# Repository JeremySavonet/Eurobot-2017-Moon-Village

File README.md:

# WestBot - MainBoard Github page

## Description
TODO

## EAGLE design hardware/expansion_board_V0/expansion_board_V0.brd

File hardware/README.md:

Hardware section:
====

TODO: XXX

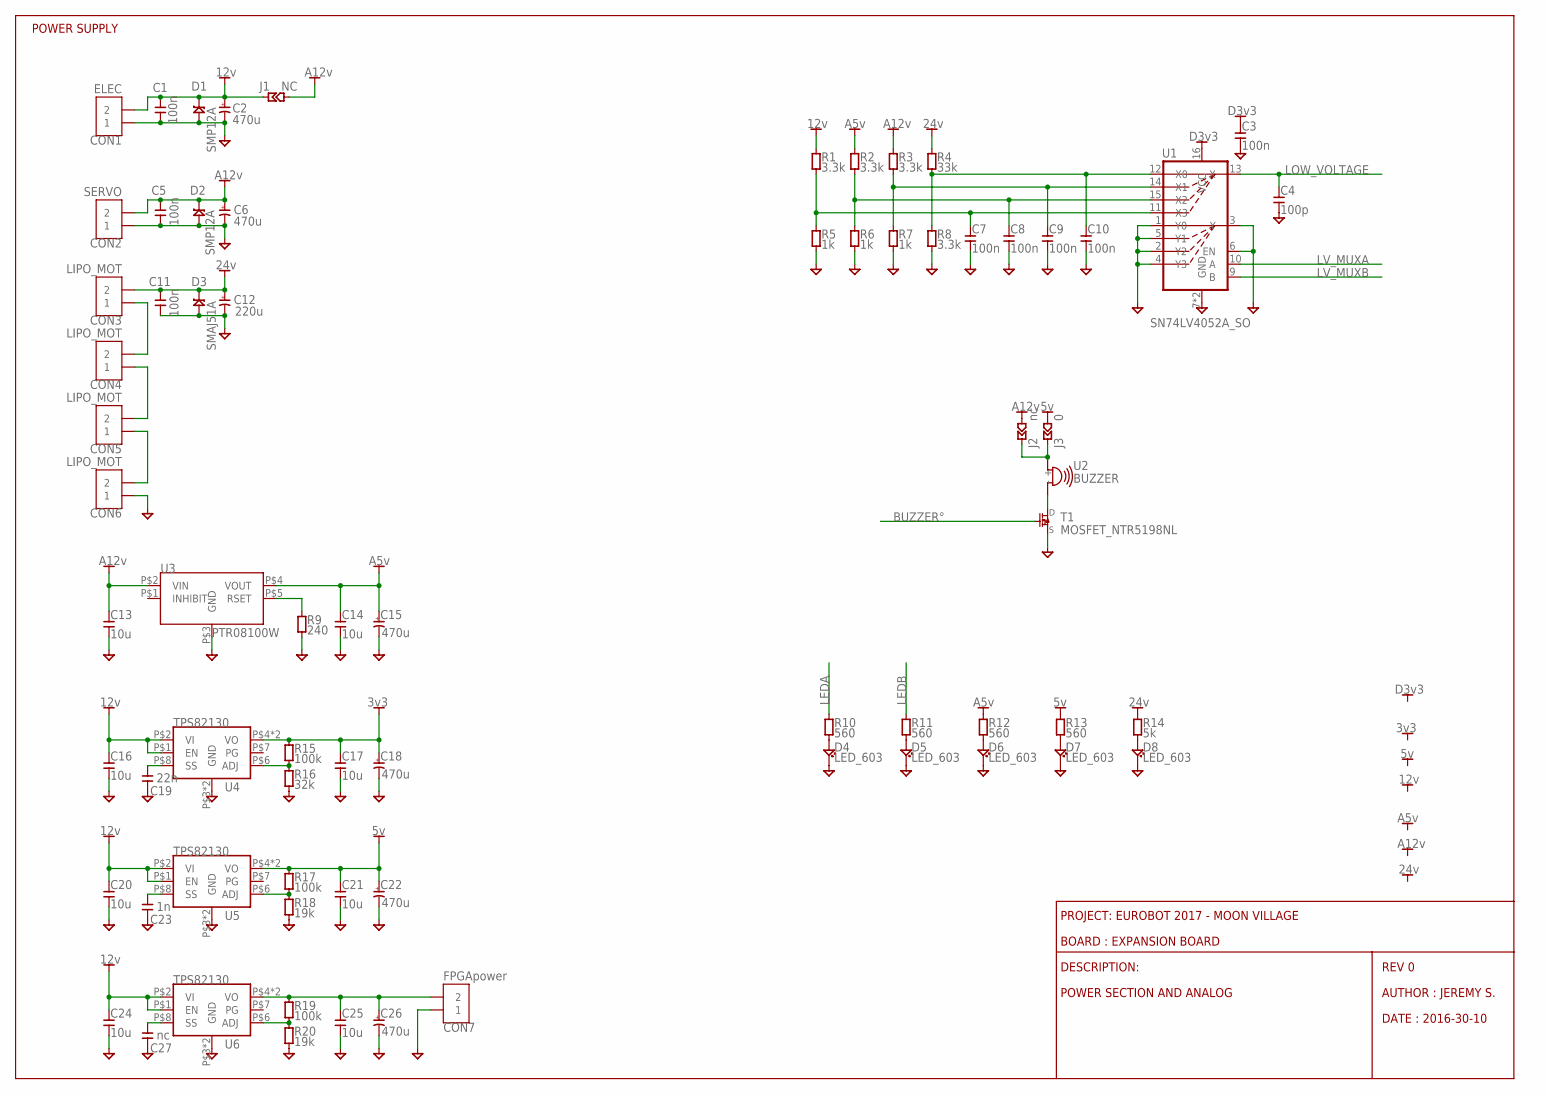
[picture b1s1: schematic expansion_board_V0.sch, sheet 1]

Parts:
C1, C3, C5, C7, C8, C9, C10: 100n; CAPC1005X55N
C2, C6, C15, C18, C22, C26: 470u; CAPAE835X1020N
C4: 100p; CAPC1005X55N
C11: 100n; CAPC2013X100N
C12: 220u; CAPAE835X1020N
C13, C14, C16, C17, C20, C21, C24, C25: 10u; CAPC2013X100N
C19: 22n; CAPC1005X55N
C23: 1n; CAPC1005X55N
C27: nc; CAPC1005X55N
CON1: ELEC; PHOENIX381P900X920-2N
CON2: SERVO; PHOENIX381P900X920-2N
CON3, CON4, CON5, CON6: LIPO_MOT; PHOENIX381P900X920-2N
CON7: FPGApower; PHOENIX381P900X920-2N
D1, D2: SMP12A; DO220AA
D3: SMAJ51A; D0214AC
D4, D5, D6, D7, D8: LED_603; LEDC1608X60N
J1: NC; JUMC1608X50AN
J2: nc; JUMC1005X50N
J3: 0; JUMC1005X50N
R1, R2, R3, R8: 3.3k; RESC1005X40N
R4: 33k; RESC1005X40N
R5, R6, R7: 1k; RESC1005X40N
R9: 240; RESC1005X40N
R10, R11, R12, R13: 560; RESC1005X40N
R14: 5k; RESC1005X40N
R15, R17, R19: 100k; RESC1005X40N
R16: 32k; RESC1005X40N
R18, R20: 19k; RESC1005X40N
T1: MOSFET_NTR5198NL; SOT95P290X130-3N
U1: SN74LV4052A_SO; SOIC127P780X200-16N
U2: BUZZER; BUZZER_CIRCLE
U3: PTR08100W
U4, U5, U6: TPS82130; SON65P310X290X153-9N

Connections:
3V3: C17.P$1, C18.+, R15.1, U4.P$4 (VO), U4.P$5 (VO); also elsewhere on the board
5V: C21.P$1, C22.+, J3.P$1 (1), R13.1, R17.1, U5.P$4 (VO), U5.P$5 (VO); also elsewhere on the board
12V: C1.1, C2.+, C16.P$1, C20.P$1, C24.P$1, CON1.P$2 (2), D1.C, J1.P$2 (2), R1.1, U4.P$1 (EN), U4.P$2 (VI), U5.P$1 (EN), U5.P$2 (VI), U6.P$1 (EN), U6.P$2 (VI); also elsewhere on the board
24V: C11.P$1, C12.+, CON3.P$2 (2), D3.C, R4.1, R14.1; also elsewhere on the board
A5V: C14.P$1, C15.+, R2.1, R12.1, U3.P$4 (VOUT); also elsewhere on the board
A12V: C5.1, C6.+, C13.P$1, CON2.P$2 (2), D2.C, J1.P$1 (1), J2.P$1 (1), R3.1, U3.P$2 (VIN); also elsewhere on the board
BUZZER°: T1.P$1 (G); also elsewhere on the board
D3V3: C3.1, U1.16 (VCC); also elsewhere on the board
GND: C1.2, C2.-, C3.2, C4.2, C5.2, C6.-, C7.2, C8.2, C9.2, C10.2, C11.P$2, C12.-, C13.P$2, C14.P$2, C15.-, C16.P$2, C17.P$2, C18.-, C19.2, C20.P$2, C21.P$2, C22.-, C23.2, C24.P$2, C25.P$2, C26.-, C27.2, CON1.P$1 (1), CON2.P$1 (1), CON6.P$1 (1), CON7.P$1 (1), D1.A, D2.A, D3.A, D4.C, D5.C, D6.C, D7.C, D8.C, R5.2, R6.2, R7.2, R8.2, R9.2, R16.2, R18.2, R20.2, T1.P$2 (S), U1.1 (Y0), U1.2 (Y2), U1.3 (Y), U1.4 (Y3), U1.5 (Y1), U1.6 (EN), U1.7 (GND), U1.8 (GND), U3.P$3 (GND), U4.P$3 (GND), U4.P$9 (GND), U5.P$3 (GND), U5.P$9 (GND), U6.P$3 (GND), U6.P$9 (GND); also elsewhere on the board
LEDA: R10.1; also elsewhere on the board
LEDB: R11.1; also elsewhere on the board
LOW_VOLTAGE: C4.1, U1.13 (X); also elsewhere on the board
LV_MUXA: U1.10 (A); also elsewhere on the board
LV_MUXB: U1.9 (B); also elsewhere on the board
unnamed: CON3.P$1 (1), CON4.P$2 (2)
unnamed: CON4.P$1 (1), CON5.P$2 (2)
unnamed: CON5.P$1 (1), CON6.P$2 (2)
unnamed: D6.A, R12.2
unnamed: R15.2, R16.1, U4.P$6 (ADJ)
unnamed: D5.A, R11.2
unnamed: D4.A, R10.2
unnamed: C19.1, U4.P$8 (SS)
unnamed: R17.2, R18.1, U5.P$6 (ADJ)
unnamed: C23.1, U5.P$8 (SS)
unnamed: R9.1, U3.P$5 (RSET)
unnamed: R19.2, R20.1, U6.P$6 (ADJ)
unnamed: C27.1, U6.P$8 (SS)
unnamed: D7.A, R13.2
unnamed: D8.A, R14.2
unnamed: C25.P$1, C26.+, CON7.P$2 (2), R19.1, U6.P$4 (VO), U6.P$5 (VO)
unnamed: C7.1, R1.2, R5.1, U1.11 (X3)
unnamed: C10.1, R4.2, R8.1, U1.12 (X0)
unnamed: C8.1, R2.2, R6.1, U1.15 (X2)
unnamed: C9.1, R3.2, R7.1, U1.14 (X1)
unnamed: T1.P$3 (D), U2.-
unnamed: J2.P$2 (2), J3.P$2 (2), U2.+

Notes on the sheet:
REV 0
AUTHOR : JEREMY S.
DATE : 2016-30-10
DESCRIPTION:
BOARD : EXPANSION BOARD
PROJECT: EUROBOT 2017 - MOON VILLAGE
POWER SECTION AND ANALOG
POWER SUPPLY

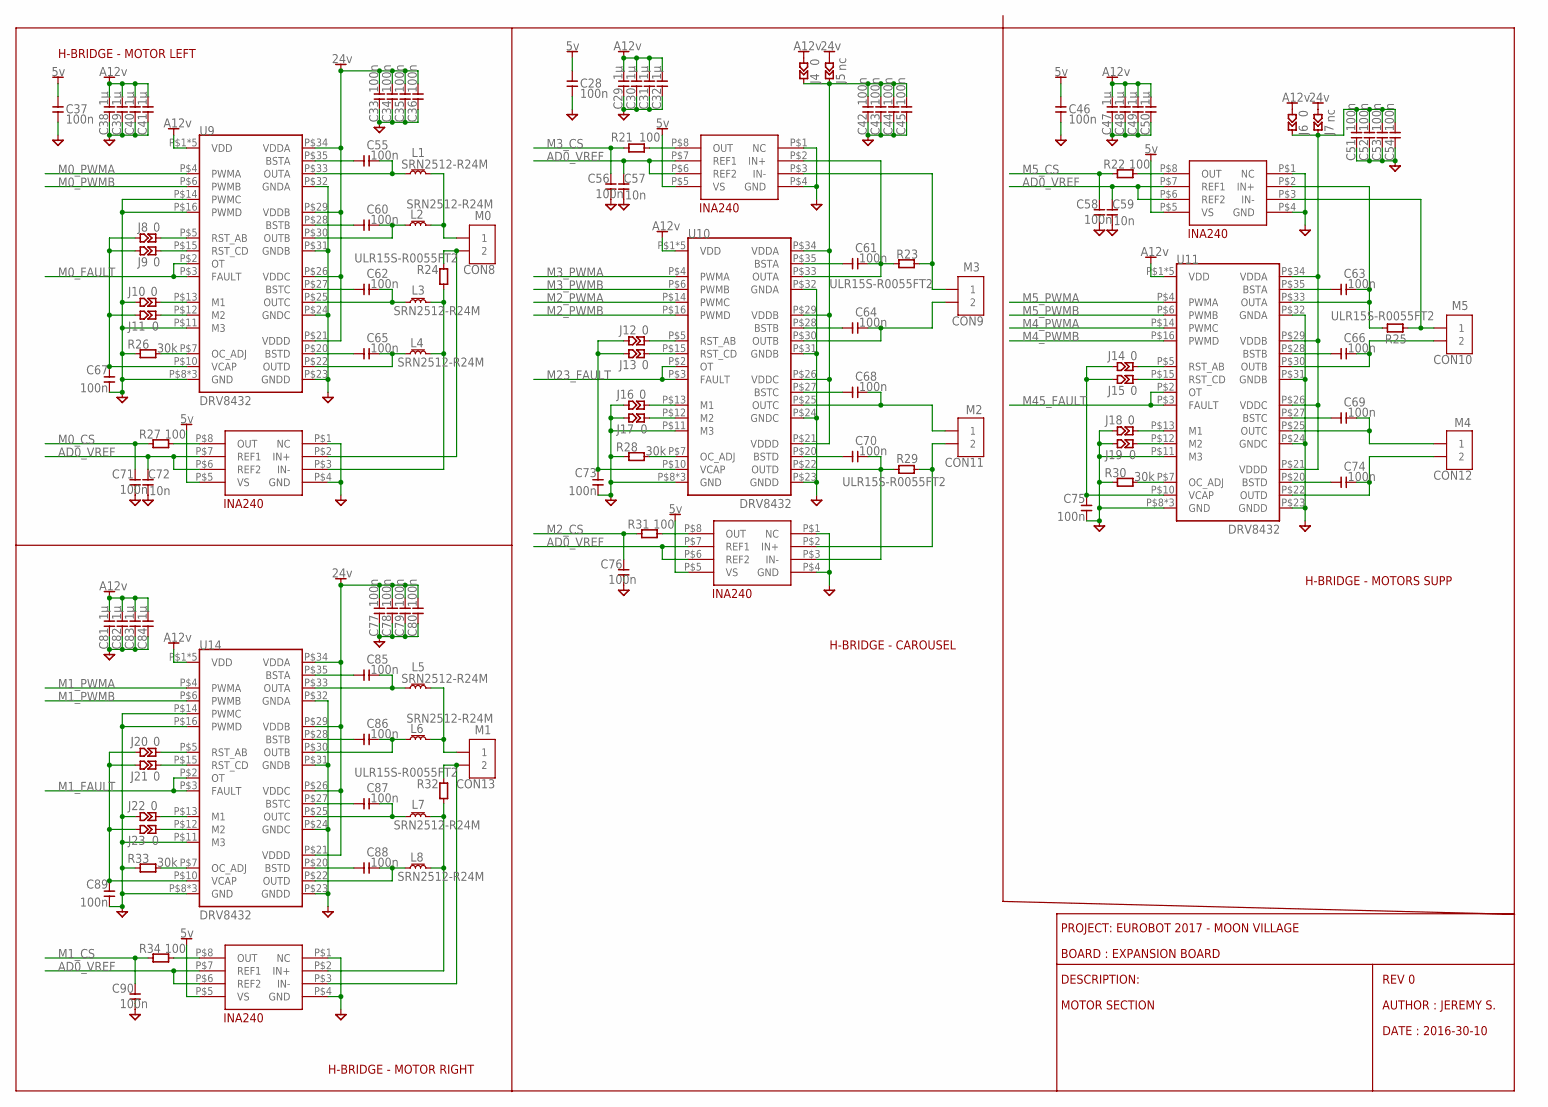
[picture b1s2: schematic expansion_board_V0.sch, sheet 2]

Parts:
C28, C37, C46, C56, C58, C67, C71, C73, C75, C76, C89, C90: 100n; CAPC1005X55N
C29, C30, C31, C32, C38, C39, C40, C41, C47, C48, C49, C50, C81, C82, C83, C84: 1µ; CAPC1608X95N
C33, C34, C35, C36, C42, C43, C44, C45, C51, C52, C53, C54, C55, C60, C61, C62, C63, C64, C65, C66, C68, C69, C70, C74, C77, C78, C79, C80, C85, C86, C87, C88: 100n; CAPC1608X95N
C57, C59, C72: 10n; CAPC1005X55N
CON8: M0; PHOENIX381P900X920-2N
CON9: M3; PHOENIX381P900X920-2N
CON10: M5; PHOENIX381P900X920-2N
CON11: M2; PHOENIX381P900X920-2N
CON12: M4; PHOENIX381P900X920-2N
CON13: M1; PHOENIX381P900X920-2N
J4, J6: 0; JUMC1608X50AN
J5, J7: nc; JUMC1608X50AN
J8, J9, J10, J11, J12, J13, J14, J15, J16, J17, J18, J19, J20, J21, J22, J23: 0; JUMC1005X50N
L1, L2, L3, L4, L5, L6, L7, L8: SRN2512-R24M; INDC2520X120N
R21, R22, R27, R31, R34: 100; RESC1005X40N
R23, R24, R25, R29, R32: ULR15S-R0055FT2; RESC_ULR15S-R0055FT2
R26, R28, R30, R33: 30k; RESC1005X40N
U7, U8, U12, U13, U15: INA240-A2; TSSOP
U9, U10, U11, U14: DRV8432; R-PDSO-G36

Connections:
5V: C28.2, C37.2, C46.2, U7.P$5 (VS), U8.P$5 (VS), U12.P$5 (VS), U13.P$5 (VS), U15.P$5 (VS); also elsewhere on the board
24V: C33.P$2, C34.P$2, C35.P$2, C36.P$2, C77.P$2, C78.P$2, C79.P$2, C80.P$2, J5.P$1 (1), J7.P$1 (1), U9.P$21 (VDDD), U9.P$26 (VDDC), U9.P$29 (VDDB), U9.P$34 (VDDA), U14.P$21 (VDDD), U14.P$26 (VDDC), U14.P$29 (VDDB), U14.P$34 (VDDA); also elsewhere on the board
A12V: C29.P$2, C30.P$2, C31.P$2, C32.P$2, C38.P$2, C39.P$2, C40.P$2, C41.P$2, C47.P$2, C48.P$2, C49.P$2, C50.P$2, C81.P$2, C82.P$2, C83.P$2, C84.P$2, J4.P$1 (1), J6.P$1 (1), U9.P$1 (VDD), U9.P$17 (VDD), U9.P$18 (VDD), U9.P$19 (VDD), U9.P$36 (VDD), U10.P$1 (VDD), U10.P$17 (VDD), U10.P$18 (VDD), U10.P$19 (VDD), U10.P$36 (VDD), U11.P$1 (VDD), U11.P$17 (VDD), U11.P$18 (VDD), U11.P$19 (VDD), U11.P$36 (VDD), U14.P$1 (VDD), U14.P$17 (VDD), U14.P$18 (VDD), U14.P$19 (VDD), U14.P$36 (VDD); also elsewhere on the board
AD0_VREF: C57.2, C59.2, C72.2, U7.P$6 (REF2), U7.P$7 (REF1), U8.P$6 (REF2), U8.P$7 (REF1), U12.P$6 (REF2), U12.P$7 (REF1), U13.P$6 (REF2), U13.P$7 (REF1), U15.P$6 (REF2), U15.P$7 (REF1); also elsewhere on the board
GND: C28.1, C29.P$1, C30.P$1, C31.P$1, C32.P$1, C33.P$1, C34.P$1, C35.P$1, C36.P$1, C37.1, C38.P$1, C39.P$1, C40.P$1, C41.P$1, C42.P$1, C43.P$1, C44.P$1, C45.P$1, C46.1, C47.P$1, C48.P$1, C49.P$1, C50.P$1, C51.P$1, C52.P$1, C53.P$1, C54.P$1, C56.1, C57.1, C58.1, C59.1, C67.1, C71.1, C72.1, C73.1, C75.1, C76.1, C77.P$1, C78.P$1, C79.P$1, C80.P$1, C81.P$1, C82.P$1, C83.P$1, C84.P$1, C89.1, C90.1, J10.P$1 (1), J16.P$1 (1), J17.P$1 (1), J18.P$1 (1), J19.P$1 (1), J22.P$1 (1), R26.2, R28.2, R30.2, R33.2, U7.P$1 (NC), U7.P$4 (GND), U8.P$1 (NC), U8.P$4 (GND), U9.P$8 (GND), U9.P$9 (GND), U9.P$11 (M3), U9.P$14 (PWMC), U9.P$16 (PWMD), U9.P$23 (GNDD), U9.P$24 (GNDC), U9.P$31 (GNDB), U9.P$32 (GNDA), U9.P$37 (GND), U10.P$8 (GND), U10.P$9 (GND), U10.P$11 (M3), U10.P$23 (GNDD), U10.P$24 (GNDC), U10.P$31 (GNDB), U10.P$32 (GNDA), U10.P$37 (GND), U11.P$8 (GND), U11.P$9 (GND), U11.P$11 (M3), U11.P$23 (GNDD), U11.P$24 (GNDC), U11.P$31 (GNDB), U11.P$32 (GNDA), U11.P$37 (GND), U12.P$1 (NC), U12.P$4 (GND), U13.P$1 (NC), U13.P$4 (GND), U14.P$8 (GND), U14.P$9 (GND), U14.P$11 (M3), U14.P$14 (PWMC), U14.P$16 (PWMD), U14.P$23 (GNDD), U14.P$24 (GNDC), U14.P$31 (GNDB), U14.P$32 (GNDA), U14.P$37 (GND), U15.P$1 (NC), U15.P$4 (GND); also elsewhere on the board
M0_CS: C71.2, R27.2; also elsewhere on the board
M0_FAULT: U9.P$2 (OT), U9.P$3 (FAULT); also elsewhere on the board
M0_PWMA: U9.P$4 (PWMA); also elsewhere on the board
M0_PWMB: U9.P$6 (PWMB); also elsewhere on the board
M1_CS: C90.2, R34.2; also elsewhere on the board
M1_FAULT: U14.P$2 (OT), U14.P$3 (FAULT); also elsewhere on the board
M1_PWMA: U14.P$4 (PWMA); also elsewhere on the board
M1_PWMB: U14.P$6 (PWMB); also elsewhere on the board
M2_CS: C76.2, R31.2; also elsewhere on the board
M2_PWMA: U10.P$14 (PWMC); also elsewhere on the board
M2_PWMB: U10.P$16 (PWMD); also elsewhere on the board
M3_CS: C56.2, R21.2; also elsewhere on the board
M3_PWMA: U10.P$4 (PWMA); also elsewhere on the board
M3_PWMB: U10.P$6 (PWMB); also elsewhere on the board
M4_PWMA: U11.P$14 (PWMC); also elsewhere on the board
M4_PWMB: U11.P$16 (PWMD); also elsewhere on the board
M5_CS: C58.2, R22.2; also elsewhere on the board
M5_PWMA: U11.P$4 (PWMA); also elsewhere on the board
M5_PWMB: U11.P$6 (PWMB); also elsewhere on the board
M23_FAULT: U10.P$2 (OT), U10.P$3 (FAULT); also elsewhere on the board
M45_FAULT: U11.P$2 (OT), U11.P$3 (FAULT); also elsewhere on the board
unnamed: J13.P$2 (2), U10.P$15 (RST_CD)
unnamed: C61.P$1, U10.P$35 (BSTA)
unnamed: C70.P$1, U10.P$20 (BSTD)
unnamed: CON8.P$2 (2), R24.P$2, U12.P$2 (IN+)
unnamed: C68.P$1, U10.P$27 (BSTC)
unnamed: CON13.P$2 (2), R32.P$2, U15.P$3 (IN-)
unnamed: C64.P$1, U10.P$28 (BSTB)
unnamed: CON10.P$1 (1), R25.P$2, U8.P$3 (IN-)
unnamed: C61.P$2, R23.P$1, U7.P$2 (IN+), U10.P$33 (OUTA)
unnamed: C74.P$2, CON12.P$2 (2), U11.P$22 (OUTD)
unnamed: C64.P$2, CON9.P$2 (2), U10.P$30 (OUTB)
unnamed: J20.P$2 (2), U14.P$5 (RST_AB)
unnamed: J16.P$2 (2), U10.P$13 (M1)
unnamed: J8.P$2 (2), U9.P$5 (RST_AB)
unnamed: J12.P$2 (2), U10.P$5 (RST_AB)
unnamed: J14.P$2 (2), U11.P$5 (RST_AB)
unnamed: J17.P$2 (2), U10.P$12 (M2)
unnamed: C68.P$2, CON11.P$1 (1), U10.P$25 (OUTC)
unnamed: C70.P$2, R29.P$1, U10.P$22 (OUTD), U13.P$3 (IN-)
unnamed: C73.2, J12.P$1 (1), J13.P$1 (1), U10.P$10 (VCAP)
unnamed: CON9.P$1 (1), R23.P$2, U7.P$3 (IN-)
unnamed: R28.1, U10.P$7 (OC_ADJ)
unnamed: R21.1, U7.P$8 (OUT)
unnamed: CON11.P$2 (2), R29.P$2, U13.P$2 (IN+)
unnamed: C63.P$1, U11.P$35 (BSTA)
unnamed: C74.P$1, U11.P$20 (BSTD)
unnamed: C69.P$1, U11.P$27 (BSTC)
unnamed: C66.P$1, U11.P$28 (BSTB)
unnamed: C63.P$2, R25.P$1, U8.P$2 (IN+), U11.P$33 (OUTA)
unnamed: C66.P$2, CON10.P$2 (2), U11.P$30 (OUTB)
unnamed: C69.P$2, CON12.P$1 (1), U11.P$25 (OUTC)
unnamed: C75.2, J14.P$1 (1), J15.P$1 (1), U11.P$10 (VCAP)
unnamed: R30.1, U11.P$7 (OC_ADJ)
unnamed: C42.P$2, C43.P$2, C44.P$2, C45.P$2, J4.P$2 (2), J5.P$2 (2), U10.P$21 (VDDD), U10.P$26 (VDDC), U10.P$29 (VDDB), U10.P$34 (VDDA)
unnamed: J15.P$2 (2), U11.P$15 (RST_CD)
unnamed: R31.1, U13.P$8 (OUT)
unnamed: J18.P$2 (2), U11.P$13 (M1)
unnamed: J19.P$2 (2), U11.P$12 (M2)
unnamed: C51.P$2, C52.P$2, C53.P$2, C54.P$2, J6.P$2 (2), J7.P$2 (2), U11.P$21 (VDDD), U11.P$26 (VDDC), U11.P$29 (VDDB), U11.P$34 (VDDA)
unnamed: C85.P$1, U14.P$35 (BSTA)
unnamed: C88.P$1, U14.P$20 (BSTD)
unnamed: C87.P$1, U14.P$27 (BSTC)
unnamed: C86.P$1, U14.P$28 (BSTB)
unnamed: C85.P$2, L5.P$2 (2), U14.P$33 (OUTA)
unnamed: C86.P$2, L6.P$2 (2), U14.P$30 (OUTB)
unnamed: C87.P$2, L7.P$2 (2), U14.P$25 (OUTC)
unnamed: C88.P$2, L8.P$2 (2), U14.P$22 (OUTD)
unnamed: C89.2, J20.P$1 (1), J21.P$1 (1), J23.P$1 (1), U14.P$10 (VCAP)
unnamed: R33.1, U14.P$7 (OC_ADJ)
unnamed: C55.P$1, U9.P$35 (BSTA)
unnamed: J21.P$2 (2), U14.P$15 (RST_CD)
unnamed: J22.P$2 (2), U14.P$13 (M1)
unnamed: J23.P$2 (2), U14.P$12 (M2)
unnamed: C65.P$1, U9.P$20 (BSTD)
unnamed: R34.1, U15.P$8 (OUT)
unnamed: C62.P$1, U9.P$27 (BSTC)
unnamed: L7.P$1 (1), L8.P$1 (1), R32.P$1, U15.P$2 (IN+)
unnamed: C60.P$1, U9.P$28 (BSTB)
unnamed: CON13.P$1 (1), L5.P$1 (1), L6.P$1 (1)
unnamed: C55.P$2, L1.P$2 (2), U9.P$33 (OUTA)
unnamed: C60.P$2, L2.P$2 (2), U9.P$30 (OUTB)
unnamed: C62.P$2, L3.P$2 (2), U9.P$25 (OUTC)
unnamed: C65.P$2, L4.P$2 (2), U9.P$22 (OUTD)
unnamed: C67.2, J8.P$1 (1), J9.P$1 (1), J11.P$1 (1), U9.P$10 (VCAP)
unnamed: R26.1, U9.P$7 (OC_ADJ)
unnamed: J9.P$2 (2), U9.P$15 (RST_CD)
unnamed: J10.P$2 (2), U9.P$13 (M1)
unnamed: J11.P$2 (2), U9.P$12 (M2)
unnamed: R27.1, U12.P$8 (OUT)
unnamed: L3.P$1 (1), L4.P$1 (1), R24.P$1, U12.P$3 (IN-)
unnamed: CON8.P$1 (1), L1.P$1 (1), L2.P$1 (1)
unnamed: R22.1, U8.P$8 (OUT)

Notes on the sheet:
REV 0
AUTHOR : JEREMY S.
DATE : 2016-30-10
DESCRIPTION:
BOARD : EXPANSION BOARD
PROJECT: EUROBOT 2017 - MOON VILLAGE
H-BRIDGE - MOTOR LEFT
MOTOR SECTION
H-BRIDGE - MOTOR RIGHT
H-BRIDGE - CAROUSEL
H-BRIDGE - MOTORS SUPP

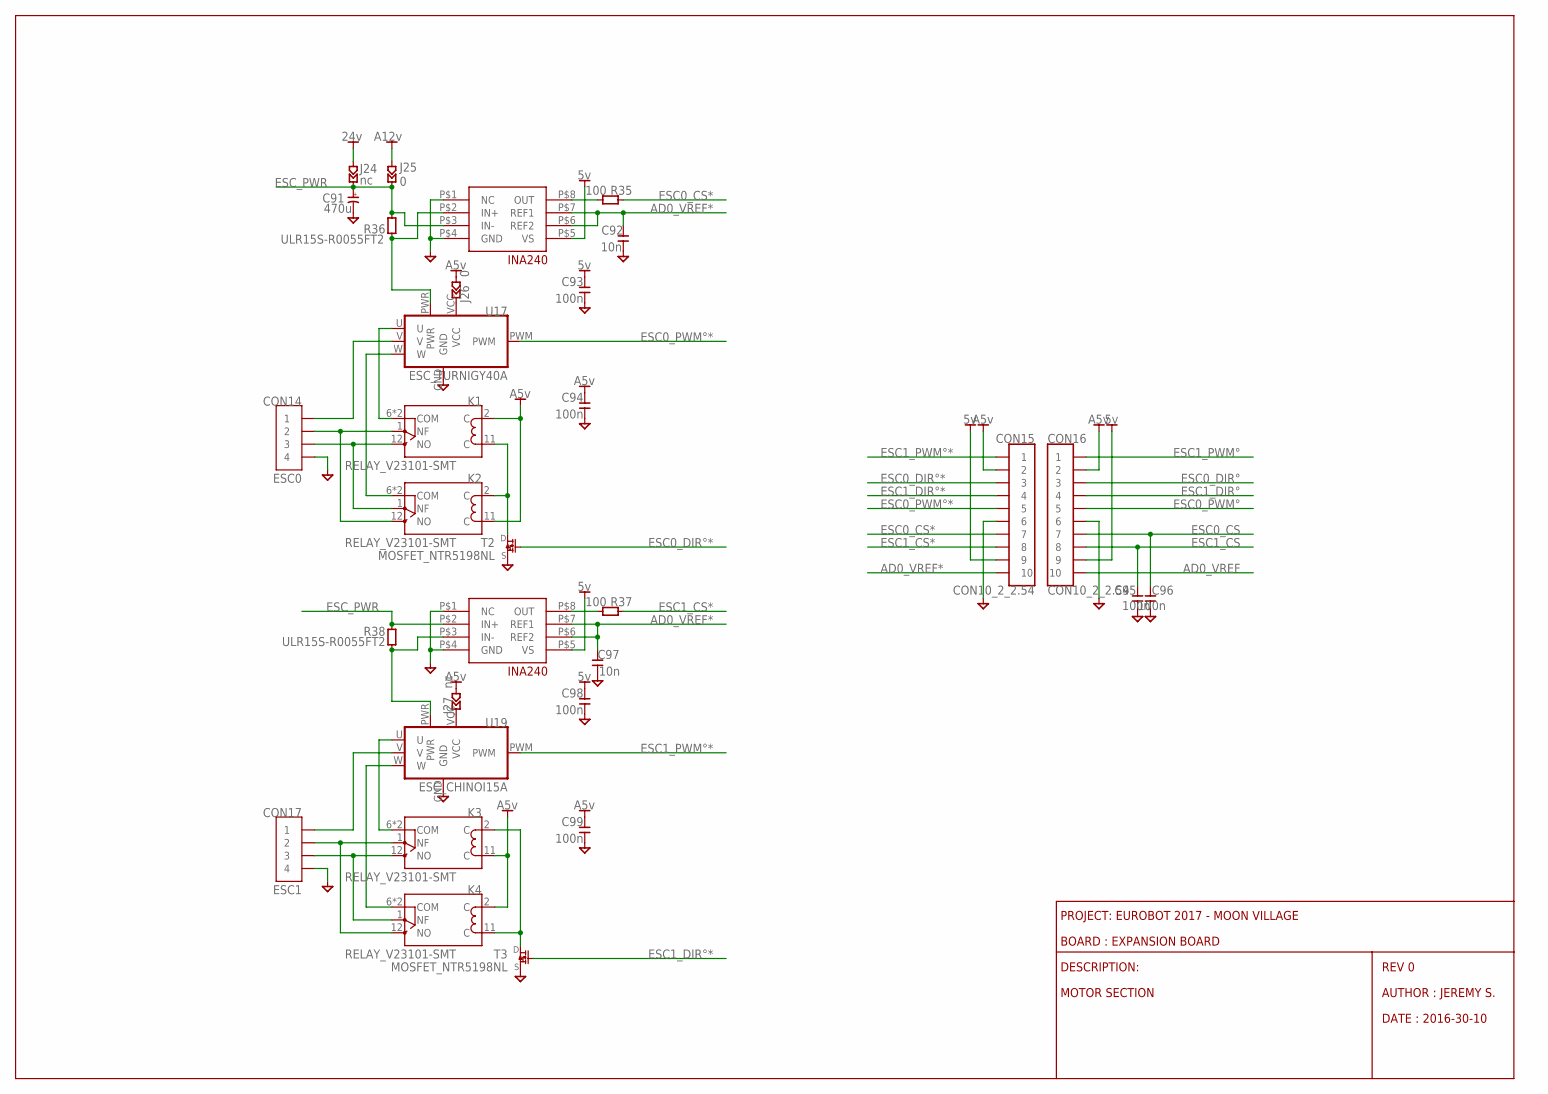
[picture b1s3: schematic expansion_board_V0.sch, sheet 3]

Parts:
C91: 470u; CAPAE835X1020N
C92, C97: 10n; CAPC1005X55N
C93, C94, C95, C96, C98, C99: 100n; CAPC1005X55N
CON14: ESC0; PHOENIX381P1662X920-4N
CON15, CON16: CON10_2_2.54; CON245P2030X890-2X5N
CON17: ESC1; PHOENIX381P1662X920-4N
J24: nc; JUMC1608X50AN
J25: 0; JUMC1608X50AN
J26: 0; JUMC1005X50N
J27: nc; JUMC1005X50N
K1, K2, K3, K4: RELAY_V23101-SMT; V23101-D0103-A201-SMT
R35, R37: 100; RESC1005X40N
R36, R38: ULR15S-R0055FT2; RESC_ULR15S-R0055FT2
T2, T3: MOSFET_NTR5198NL; SOT95P290X130-3N
U16, U18: INA240-A2; TSSOP
U17: ESC_TURNIGY40A
U19: ESC_CHINOI15A

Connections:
5V: C93.1, C98.1, CON15.P$9 (9), CON16.P$9 (9), U16.P$5 (VS), U18.P$5 (VS); also elsewhere on the board
24V: J24.P$1 (1); also elsewhere on the board
A5V: C94.1, C99.1, CON15.P$2 (2), CON16.P$2 (2), J26.P$1 (1), J27.P$1 (1), K1.2 (C), K2.11 (C), K3.11 (C), K4.2 (C); also elsewhere on the board
A12V: J25.P$1 (1); also elsewhere on the board
AD0_VREF: CON16.P$10 (10); also elsewhere on the board
AD0_VREF*: C92.2, C97.2, CON15.P$10 (10), U16.P$6 (REF2), U16.P$7 (REF1), U18.P$6 (REF2), U18.P$7 (REF1)
ESC0_CS: C96.2, CON16.P$7 (7); also elsewhere on the board
ESC0_CS*: CON15.P$7 (7), R35.2
ESC0_DIR°: CON16.P$3 (3); also elsewhere on the board
ESC0_DIR°*: CON15.P$3 (3), T2.P$1 (G)
ESC0_PWM°: CON16.P$5 (5); also elsewhere on the board
ESC0_PWM°*: CON15.P$5 (5), U17.PWM
ESC1_CS: C95.2, CON16.P$8 (8); also elsewhere on the board
ESC1_CS*: CON15.P$8 (8), R37.2
ESC1_DIR°: CON16.P$4 (4); also elsewhere on the board
ESC1_DIR°*: CON15.P$4 (4), T3.P$1 (G)
ESC1_PWM°: CON16.P$1 (1); also elsewhere on the board
ESC1_PWM°*: CON15.P$1 (1), U19.PWM
ESC_PWR: C91.+, J24.P$2 (2), J25.P$2 (2), R36.P$2, R38.P$2, U16.P$3 (IN-), U18.P$2 (IN+)
GND: C91.-, C92.1, C93.2, C94.2, C95.1, C96.1, C97.1, C98.2, C99.2, CON14.P$4 (4), CON15.P$6 (6), CON16.P$6 (6), CON17.P$4 (4), T2.P$2 (S), T3.P$2 (S), U16.P$1 (NC), U16.P$4 (GND), U17.GND, U18.P$1 (NC), U18.P$4 (GND), U19.GND; also elsewhere on the board
unnamed: K3.2 (C), K4.11 (C), T3.P$3 (D)
unnamed: K1.11 (C), K2.2 (C), T2.P$3 (D)
unnamed: K2.6 (COM), K2.7 (COM), U17.W
unnamed: K1.6 (COM), K1.7 (COM), U17.U
unnamed: CON14.P$2 (2), K1.1 (NF), K2.12 (NO)
unnamed: CON14.P$3 (3), K1.12 (NO), K2.1 (NF)
unnamed: CON14.P$1 (1), U17.V
unnamed: R35.1, U16.P$8 (OUT)
unnamed: R36.P$1, U16.P$2 (IN+), U17.PWR
unnamed: J27.P$2 (2), U19.VCC
unnamed: J26.P$2 (2), U17.VCC
unnamed: K4.6 (COM), K4.7 (COM), U19.W
unnamed: K3.6 (COM), K3.7 (COM), U19.U
unnamed: CON17.P$2 (2), K3.1 (NF), K4.12 (NO)
unnamed: CON17.P$3 (3), K3.12 (NO), K4.1 (NF)
unnamed: CON17.P$1 (1), U19.V
unnamed: R37.1, U18.P$8 (OUT)
unnamed: R38.P$1, U18.P$3 (IN-), U19.PWR

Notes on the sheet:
REV 0
AUTHOR : JEREMY S.
DATE : 2016-30-10
DESCRIPTION:
BOARD : EXPANSION BOARD
PROJECT: EUROBOT 2017 - MOON VILLAGE
MOTOR SECTION

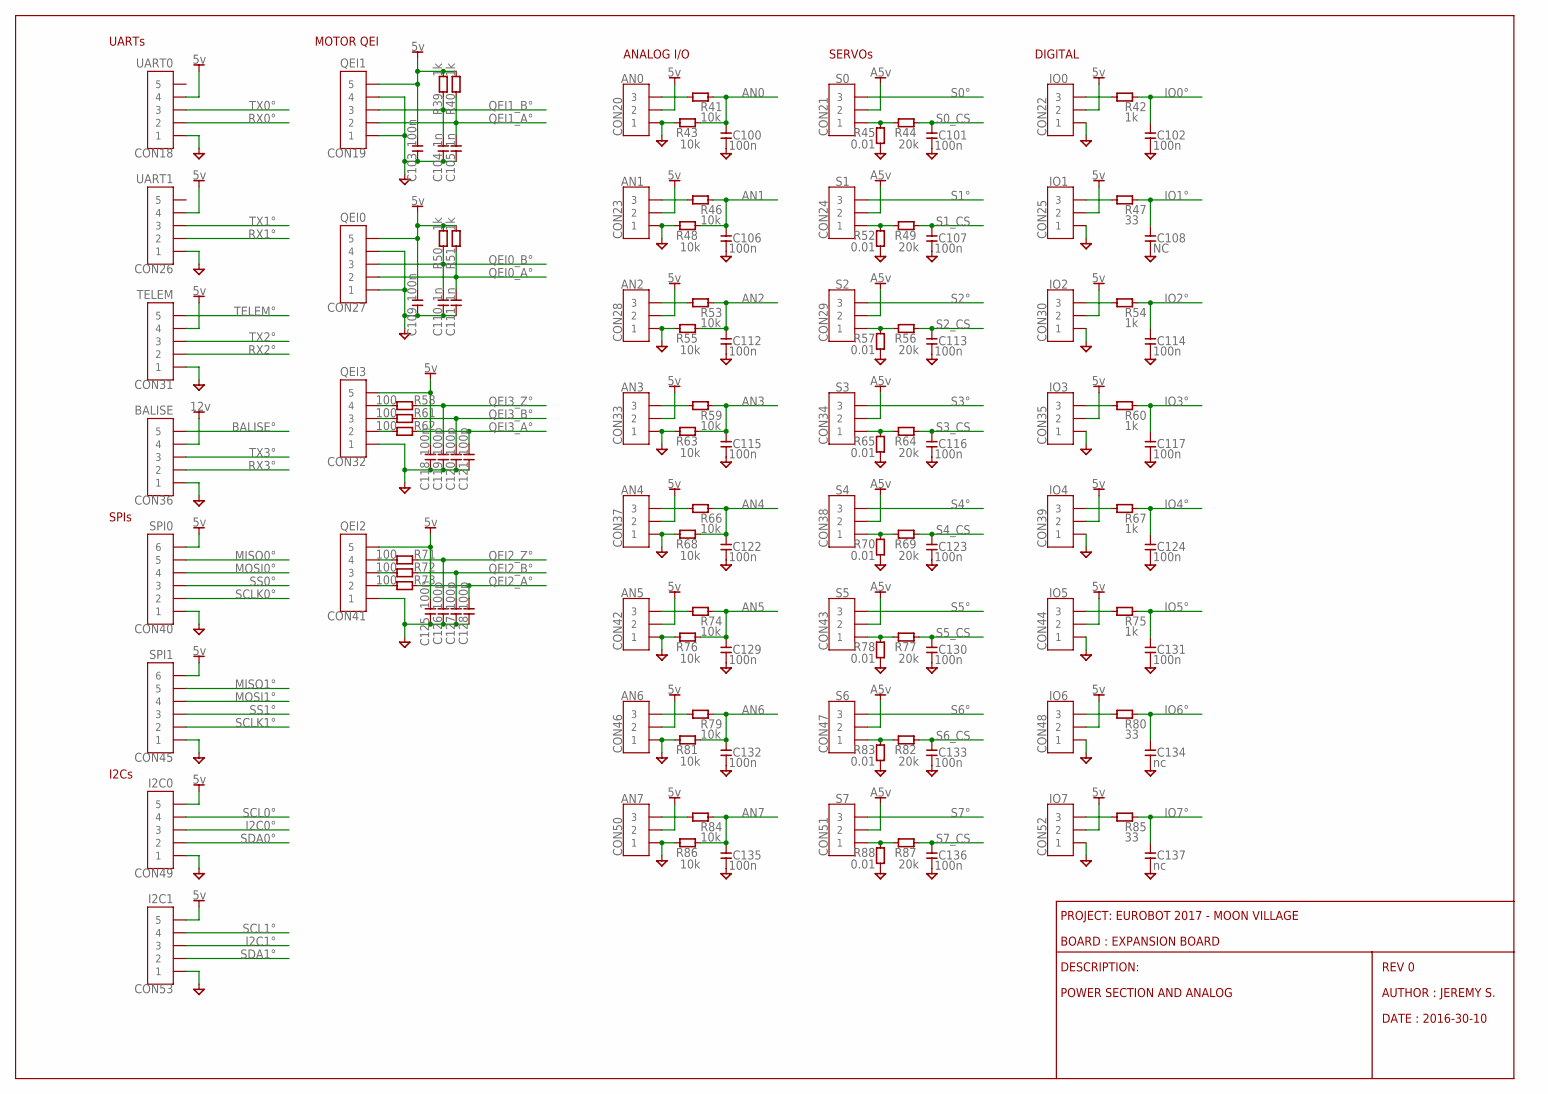
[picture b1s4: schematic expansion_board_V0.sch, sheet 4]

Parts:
C100, C101, C102, C103, C106, C107, C109, C112, C113, C114, C115, C116, C117, C118, C122, C123, C124, C125, C129, C130, C131, C132, C133, C135, C136: 100n; CAPC1005X55N
C104, C105, C110, C111: 1n; CAPC1005X55N
C108: NC; CAPC1005X55N
C119, C120, C121, C126, C127, C128: 100p; CAPC1005X55N
C134, C137: nc; CAPC1005X55N
CON18: UART0; CON254P1270X400-5S
CON19: QEI1; CON254P1270X400-5S
CON20: AN0; CON254P762X400-3SMT
CON21: S0; CON254P762X400-3SMT
CON22: IO0; CON254P762X400-3SMT
CON23: AN1; CON254P762X400-3SMT
CON24: S1; CON254P762X400-3SMT
CON25: IO1; CON254P762X400-3SMT
CON26: UART1; CON254P1270X400-5S
CON27: QEI0; CON254P1270X400-5S
CON28: AN2; CON254P762X400-3SMT
CON29: S2; CON254P762X400-3SMT
CON30: IO2; CON254P762X400-3SMT
CON31: TELEM; CON254P1270X400-5S
CON32: QEI3; CON254P1270X400-5S
CON33: AN3; CON254P762X400-3SMT
CON34: S3; CON254P762X400-3SMT
CON35: IO3; CON254P762X400-3SMT
CON36: BALISE; CON254P1270X400-5S
CON37: AN4; CON254P762X400-3SMT
CON38: S4; CON254P762X400-3SMT
CON39: IO4; CON254P762X400-3SMT
CON40: SPI0; CON254P1524X400-6N-S
CON41: QEI2; CON254P1270X400-5S
CON42: AN5; CON254P762X400-3SMT
CON43: S5; CON254P762X400-3SMT
CON44: IO5; CON254P762X400-3SMT
CON45: SPI1; CON254P1524X400-6N-S
CON46: AN6; CON254P762X400-3SMT
CON47: S6; CON254P762X400-3SMT
CON48: IO6; CON254P762X400-3SMT
CON49: I2C0; CON254P1270X400-5S
CON50: AN7; CON254P762X400-3SMT
CON51: S7; CON254P762X400-3SMT
CON52: IO7; CON254P762X400-3SMT
CON53: I2C1; CON254P1270X400-5S
R39, R40, R42, R50, R51, R54, R60, R67, R75: 1k; RESC1005X40N
R41, R43, R46, R48, R53, R55, R59, R63, R66, R68, R74, R76, R79, R81, R84, R86: 10k; RESC1005X40N
R44, R49, R56, R64, R69, R77, R82, R87: 20k; RESC1005X40N
R45, R52, R57, R65, R70, R78, R83, R88: 0.01; RESC1608X50AN
R47, R80, R85: 33; RESC1005X40N
R58, R61, R62, R71, R72, R73: 100; RESC1005X40N

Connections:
5V: C103.2, C109.2, C118.2, C125.2, CON18.4, CON19.5, CON20.2, CON22.2, CON23.2, CON25.2, CON26.4, CON27.5, CON28.2, CON30.2, CON31.4, CON32.5, CON33.2, CON35.2, CON37.2, CON39.2, CON40.6, CON41.5, CON42.2, CON44.2, CON45.6, CON46.2, CON48.2, CON49.5, CON50.2, CON52.2, CON53.5, R39.2, R40.2, R50.2, R51.2; also elsewhere on the board
12V: CON36.4; also elsewhere on the board
A5V: CON21.2, CON24.2, CON29.2, CON34.2, CON38.2, CON43.2, CON47.2, CON51.2; also elsewhere on the board
AN0: C100.2, R41.2, R43.1; also elsewhere on the board
AN1: C106.2, R46.2, R48.1; also elsewhere on the board
AN2: C112.2, R53.2, R55.1; also elsewhere on the board
AN3: C115.2, R59.2, R63.1; also elsewhere on the board
AN4: C122.2, R66.2, R68.1; also elsewhere on the board
AN5: C129.2, R74.2, R76.1; also elsewhere on the board
AN6: C132.2, R79.2, R81.1; also elsewhere on the board
AN7: C135.2, R84.2, R86.1; also elsewhere on the board
BALISE°: CON36.5; also elsewhere on the board
GND: C100.1, C101.1, C102.1, C103.1, C104.1, C105.1, C106.1, C107.1, C108.1, C109.1, C110.1, C111.1, C112.1, C113.1, C114.1, C115.1, C116.1, C117.1, C118.1, C119.1, C120.1, C121.1, C122.1, C123.1, C124.1, C125.1, C126.1, C127.1, C128.1, C129.1, C130.1, C131.1, C132.1, C133.1, C134.1, C135.1, C136.1, C137.1, CON18.1, CON19.1, CON19.4, CON20.1, CON22.1, CON23.1, CON25.1, CON26.1, CON27.1, CON27.4, CON28.1, CON30.1, CON31.1, CON32.1, CON33.1, CON35.1, CON36.1, CON37.1, CON39.1, CON40.1, CON41.1, CON42.1, CON44.1, CON45.1, CON46.1, CON48.1, CON49.1, CON50.1, CON52.1, CON53.1, R43.2, R45.P$2, R48.2, R52.P$2, R55.2, R57.P$2, R63.2, R65.P$2, R68.2, R70.P$2, R76.2, R78.P$2, R81.2, R83.P$2, R86.2, R88.P$2; also elsewhere on the board
I2C0°: CON49.3; also elsewhere on the board
I2C1°: CON53.3; also elsewhere on the board
IO0°: C102.2, R42.2; also elsewhere on the board
IO1°: C108.2, R47.2; also elsewhere on the board
IO2°: C114.2, R54.2; also elsewhere on the board
IO3°: C117.2, R60.2; also elsewhere on the board
IO4°: C124.2, R67.2; also elsewhere on the board
IO5°: C131.2, R75.2; also elsewhere on the board
IO6°: C134.2, R80.2; also elsewhere on the board
IO7°: C137.2, R85.2; also elsewhere on the board
MISO0°: CON40.5; also elsewhere on the board
MISO1°: CON45.5; also elsewhere on the board
MOSI0°: CON40.4; also elsewhere on the board
MOSI1°: CON45.4; also elsewhere on the board
unnamed: CON21.1, R44.2, R45.P$1
unnamed: CON24.1, R49.2, R52.P$1
unnamed: CON29.1, R56.2, R57.P$1
unnamed: CON50.3, R84.1
unnamed: CON20.3, R41.1
unnamed: CON23.3, R46.1
unnamed: CON28.3, R53.1
unnamed: CON33.3, R59.1
unnamed: CON37.3, R66.1
unnamed: CON34.1, R64.2, R65.P$1
unnamed: CON38.1, R69.2, R70.P$1
unnamed: CON43.1, R77.2, R78.P$1
unnamed: CON47.1, R82.2, R83.P$1
unnamed: CON51.1, R87.2, R88.P$1
unnamed: CON42.3, R74.1
unnamed: CON46.3, R79.1
unnamed: CON52.3, R85.1
unnamed: CON22.3, R42.1
unnamed: CON25.3, R47.1
unnamed: CON30.3, R54.1
unnamed: CON35.3, R60.1
unnamed: CON39.3, R67.1
unnamed: CON44.3, R75.1
unnamed: CON48.3, R80.1
unnamed: CON41.4, R71.2
unnamed: CON41.3, R72.2
unnamed: CON41.2, R73.2
unnamed: CON32.4, R58.2
unnamed: CON32.3, R61.2
unnamed: CON32.2, R62.2
QEI0_A°: C111.2, CON27.2, R51.1; also elsewhere on the board
QEI0_B°: C110.2, CON27.3, R50.1; also elsewhere on the board
QEI1_A°: C105.2, CON19.2, R40.1; also elsewhere on the board
QEI1_B°: C104.2, CON19.3, R39.1; also elsewhere on the board
QEI2_A°: C128.2, R73.1; also elsewhere on the board
QEI2_B°: C127.2, R72.1; also elsewhere on the board
QEI2_Z°: C126.2, R71.1; also elsewhere on the board
QEI3_A°: C121.2, R62.1; also elsewhere on the board
QEI3_B°: C120.2, R61.1; also elsewhere on the board
QEI3_Z°: C119.2, R58.1; also elsewhere on the board
RX0°: CON18.2; also elsewhere on the board
RX1°: CON26.2; also elsewhere on the board
RX2°: CON31.2; also elsewhere on the board
RX3°: CON36.2; also elsewhere on the board
S0_CS: C101.2, R44.1; also elsewhere on the board
S0°: CON21.3; also elsewhere on the board
S1_CS: C107.2, R49.1; also elsewhere on the board
S1°: CON24.3; also elsewhere on the board
S2_CS: C113.2, R56.1; also elsewhere on the board
S2°: CON29.3; also elsewhere on the board
S3_CS: C116.2, R64.1; also elsewhere on the board
S3°: CON34.3; also elsewhere on the board
S4_CS: C123.2, R69.1; also elsewhere on the board
S4°: CON38.3; also elsewhere on the board
S5_CS: C130.2, R77.1; also elsewhere on the board
S5°: CON43.3; also elsewhere on the board
S6_CS: C133.2, R82.1; also elsewhere on the board
S6°: CON47.3; also elsewhere on the board
S7_CS: C136.2, R87.1; also elsewhere on the board
S7°: CON51.3; also elsewhere on the board
SCL0°: CON49.4; also elsewhere on the board
SCL1°: CON53.4; also elsewhere on the board
SCLK0°: CON40.2; also elsewhere on the board
SCLK1°: CON45.2; also elsewhere on the board
SDA0°: CON49.2; also elsewhere on the board
SDA1°: CON53.2; also elsewhere on the board
SS0°: CON40.3; also elsewhere on the board
SS1°: CON45.3; also elsewhere on the board
TELEM°: CON31.5; also elsewhere on the board
TX0°: CON18.3; also elsewhere on the board
TX1°: CON26.3; also elsewhere on the board
TX2°: CON31.3; also elsewhere on the board
TX3°: CON36.3; also elsewhere on the board

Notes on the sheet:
SERVOs
ANALOG I/O
REV 0
AUTHOR : JEREMY S.
DATE : 2016-30-10
DESCRIPTION:
BOARD : EXPANSION BOARD
PROJECT: EUROBOT 2017 - MOON VILLAGE
POWER SECTION AND ANALOG
DIGITAL
UARTs
SPIs
I2Cs
MOTOR QEI

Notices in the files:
software/HPS_FPGA_LED/fpga/DE10.qsf:
Copyright (C) 1991-2016 Altera Corporation. All rights reserved.
parts and their libraries:
SparkFun-Connectors: Licensing: Creative Commons ShareAlike 4.0 International - https://creativecommons.org/licenses/by-sa/4.0
